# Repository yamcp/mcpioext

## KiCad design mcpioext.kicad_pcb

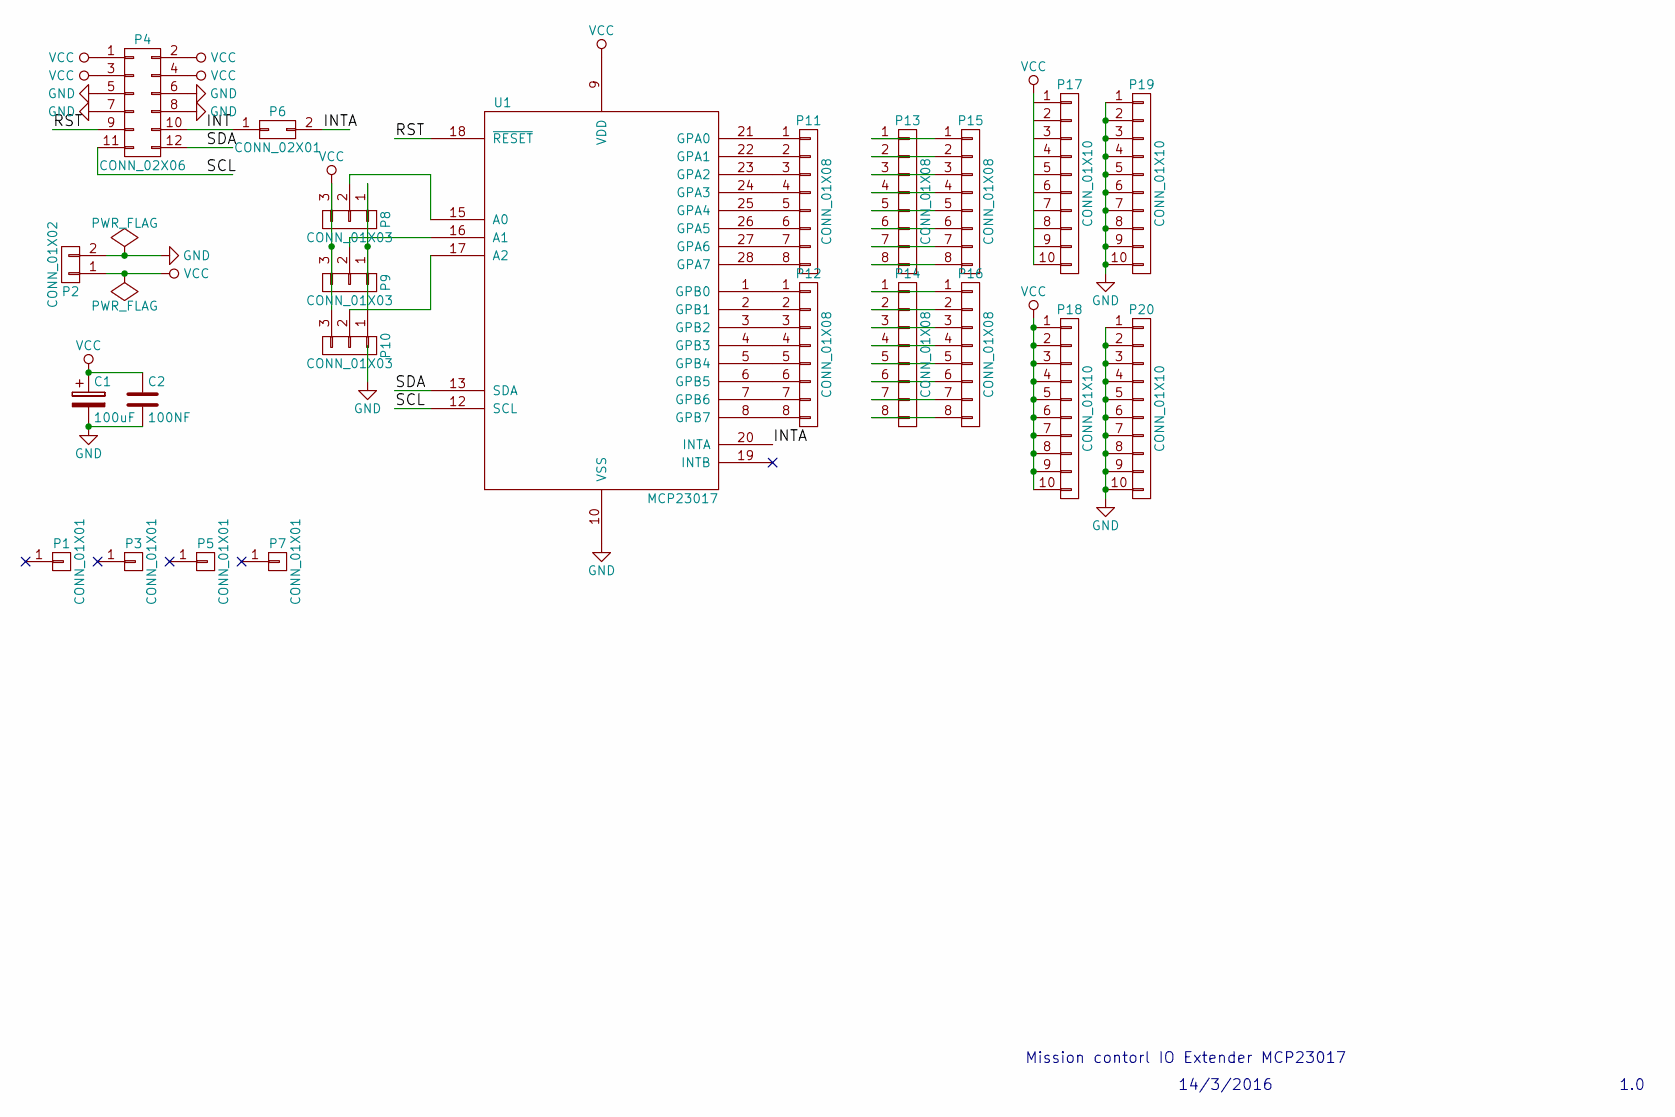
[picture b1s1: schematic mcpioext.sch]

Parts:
C1: 100uF; C_Radial_D5_L11_P2
C2: 100NF; C_Rect_L7_W2_P5
P1, P3, P5, P7: CONN_01X01; MountingHole_3.2mm_M3_Pad
P2: CONN_01X02; bornier2
P4: CONN_02X06; IDC_Header_Straight_12pins
P6: CONN_02X01; Pin_Header_Straight_2x01
P8, P9, P10: CONN_01X03; Pin_Header_Straight_1x03
P11, P12, P13, P14, P15, P16: CONN_01X08; Pin_Header_Straight_1x08
P17, P18, P19, P20: CONN_01X10; Pin_Header_Straight_1x10
U1: MCP23017; DIP-28_W7.62mm_LongPads

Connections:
/INT: P4.10, P6.1
/INTA: P6.2, U1.20 (INTA)
/RST: P4.9, U1.18 (~RESET)
/SCL: P4.11, U1.12 (SCL)
/SDA: P4.12, U1.13 (SDA)
GND: C1.2, C2.2, P2.2, P4.5, P4.6, P4.7, P4.8, P19.1, P19.2, P19.3, P19.4, P19.5, P19.6, P19.7, P19.8, P19.9, P19.10, P20.1, P20.2, P20.3, P20.4, P20.5, P20.6, P20.7, P20.8, P20.9, P20.10, U1.10 (VSS)
unnamed: P8.2, U1.15 (A0)
unnamed: P9.2, U1.16 (A1)
unnamed: P8.1, P9.1, P10.1
unnamed: P10.2, U1.17 (A2)
unnamed: P11.1, U1.21 (GPA0)
unnamed: P11.2, U1.22 (GPA1)
unnamed: P11.3, U1.23 (GPA2)
unnamed: P11.4, U1.24 (GPA3)
unnamed: P11.5, U1.25 (GPA4)
unnamed: P11.6, U1.26 (GPA5)
unnamed: P11.7, U1.27 (GPA6)
unnamed: P11.8, U1.28 (GPA7)
unnamed: P12.1, U1.1 (GPB0)
unnamed: P12.2, U1.2 (GPB1)
unnamed: P12.3, U1.3 (GPB2)
unnamed: P12.4, U1.4 (GPB3)
unnamed: P12.5, U1.5 (GPB4)
unnamed: P12.6, U1.6 (GPB5)
unnamed: P12.7, U1.7 (GPB6)
unnamed: P12.8, U1.8 (GPB7)
unnamed: P13.1, P15.1
unnamed: P13.2, P15.2
unnamed: P13.3, P15.3
unnamed: P13.4, P15.4
unnamed: P13.5, P15.5
unnamed: P13.6, P15.6
unnamed: P13.7, P15.7
unnamed: P13.8, P15.8
unnamed: P14.1, P16.1
unnamed: P14.2, P16.2
unnamed: P14.3, P16.3
unnamed: P14.4, P16.4
unnamed: P14.5, P16.5
unnamed: P14.6, P16.6
unnamed: P14.7, P16.7
unnamed: P14.8, P16.8
VCC: C1.1, C2.1, P2.1, P4.1, P4.2, P4.3, P4.4, P8.3, P9.3, P10.3, P17.10, P18.1, P18.2, P18.3, P18.4, P18.5, P18.6, P18.7, P18.8, P18.9, P18.10, U1.9 (VDD)

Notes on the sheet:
Mission contorl IO Extender MCP23017
14/3/2016
1.0

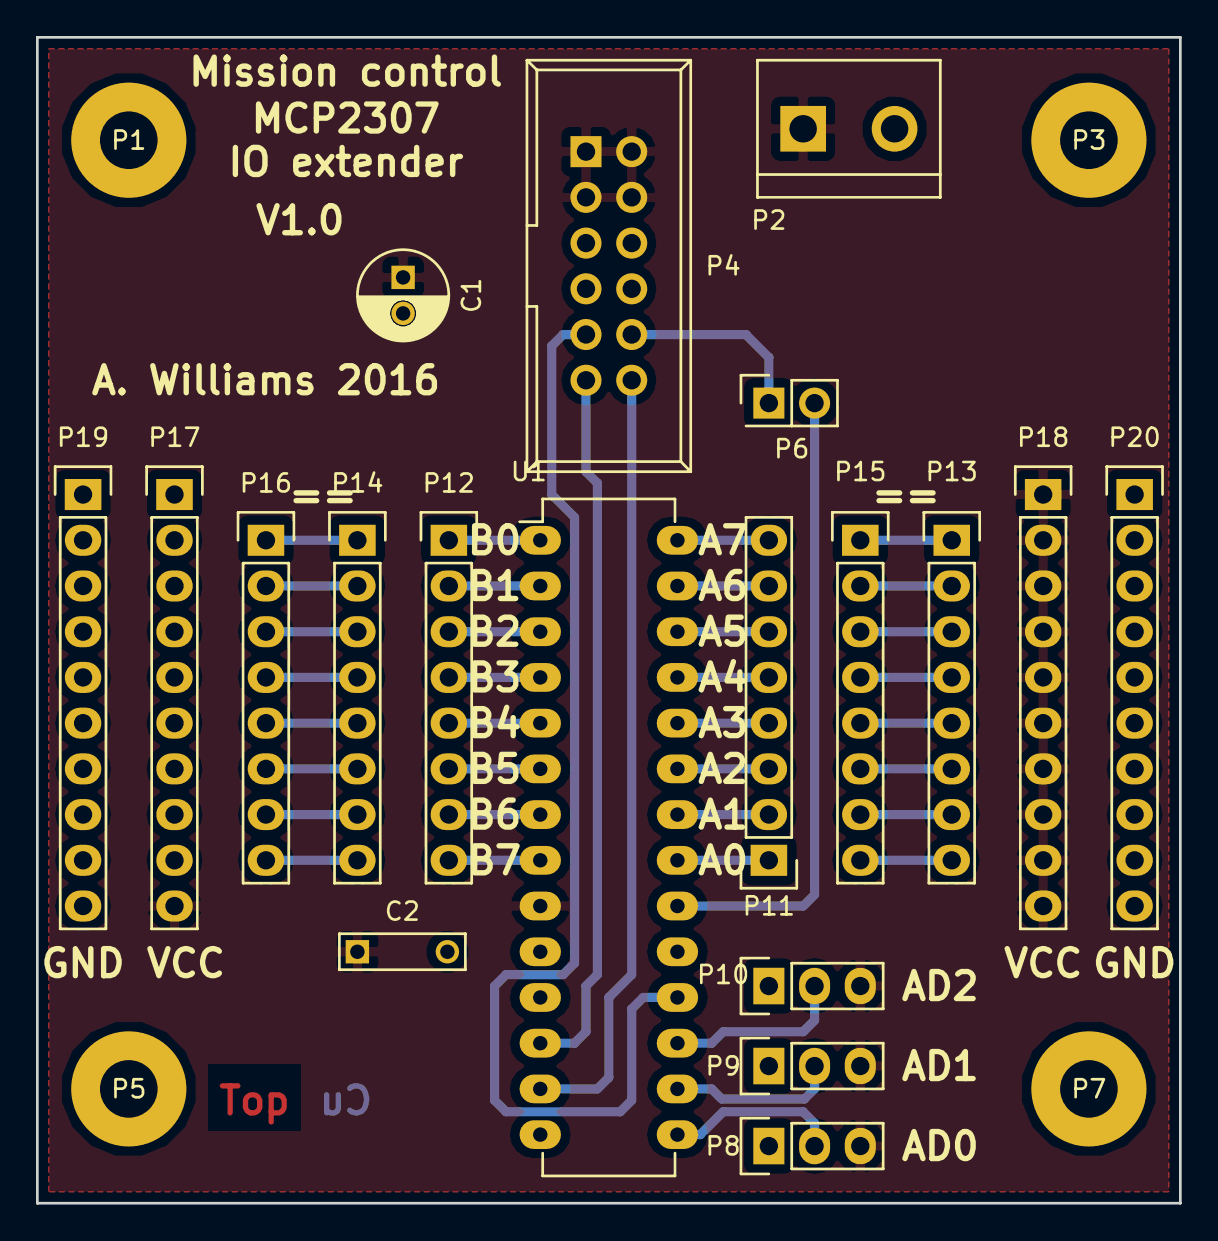
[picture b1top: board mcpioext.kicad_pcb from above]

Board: 2 copper layers, 63.5 x 64.8 mm, 23 parts (0 on the bottom side), 43 nets.
